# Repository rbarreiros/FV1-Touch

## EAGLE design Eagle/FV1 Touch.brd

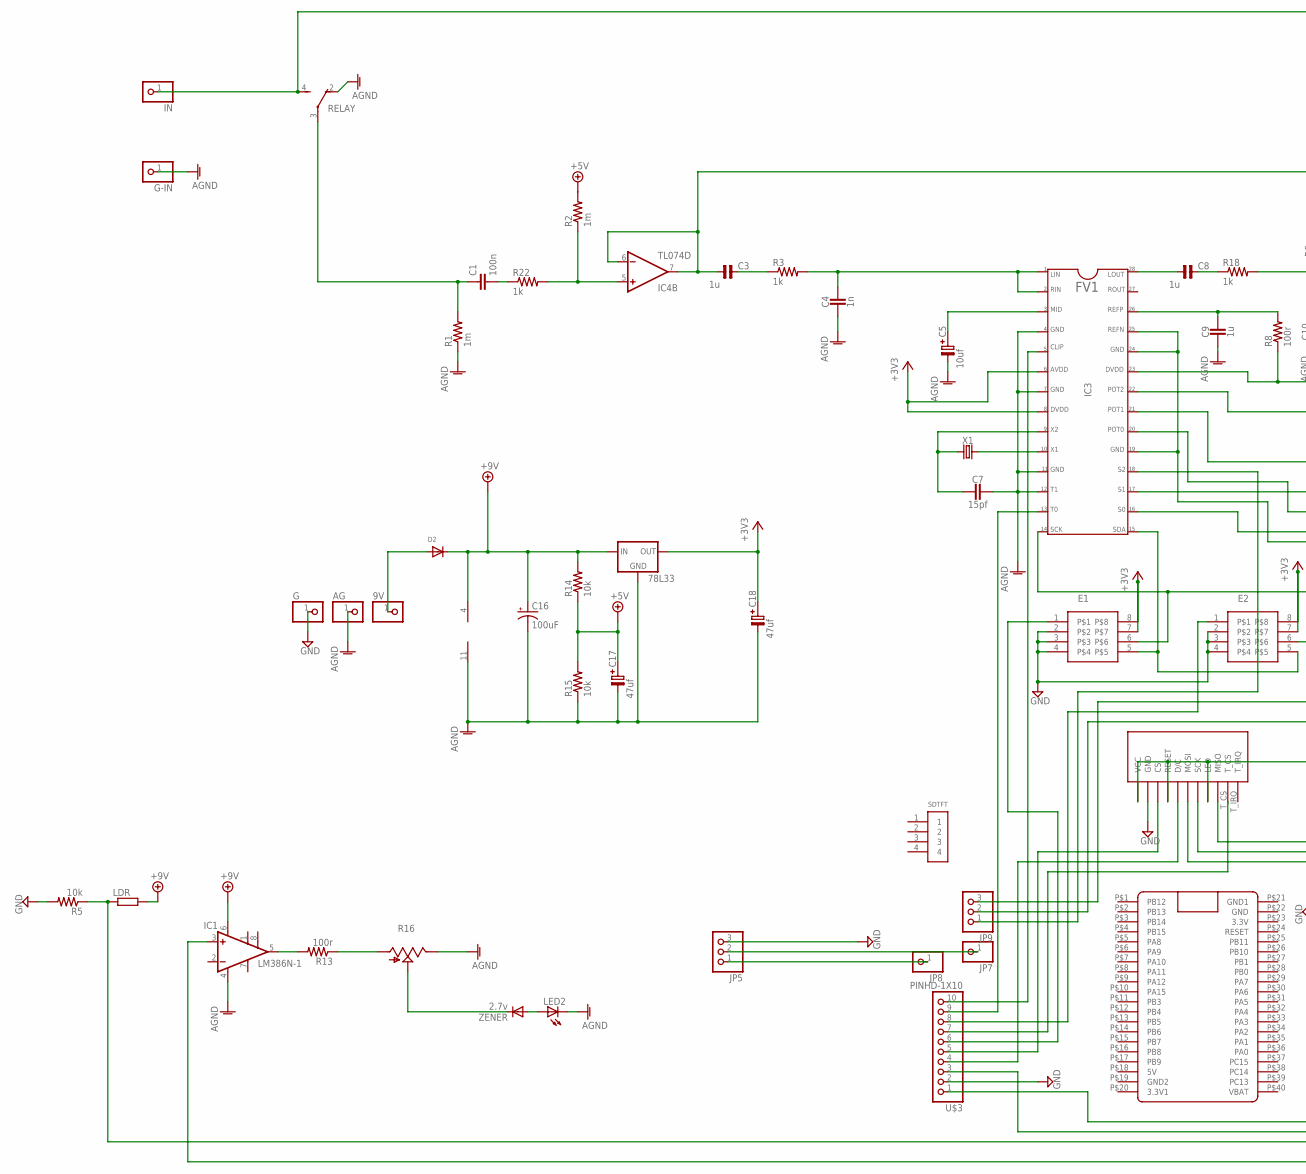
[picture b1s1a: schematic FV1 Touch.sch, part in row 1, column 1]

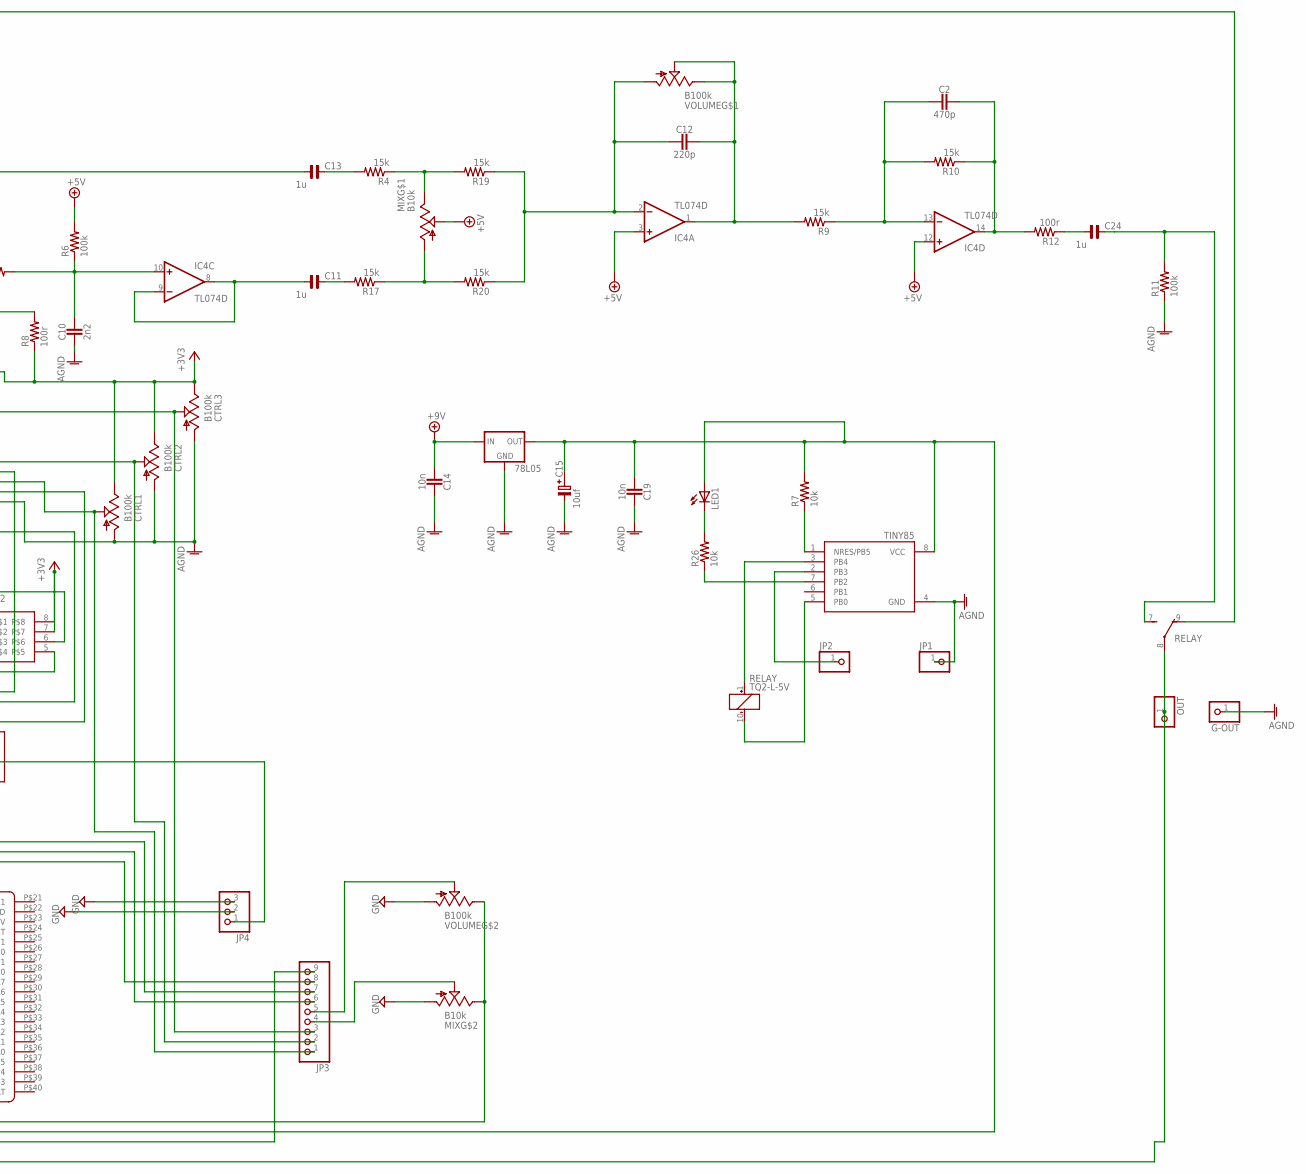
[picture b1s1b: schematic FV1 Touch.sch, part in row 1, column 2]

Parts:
9V: PINHD-1X1; 1X01
78L05, 78L33: 78LXX-SOT89; SOT89
AG: PINHD-1X1; 1X01
C1: 100n; C5B3
C2: 470p; RESISTOR_C1206
C3, C8, C11, C13, C24: 1u; C5,0-7,5X3,0
C4: 1n; RESISTOR_C1206
C5, C15: 10uf; SV-C
C7: 15pf; RESISTOR_C1206
C9: 1u; RESISTOR_C1206
C10: 2n2; RESISTOR_C1206
C12: 220p; RESISTOR_C1206
C14, C19: 10n; RESISTOR_C1206
C16: 100uF; PANASONIC_D
C17, C18: 47uf; SV-C
CTRL1, CTRL2, CTRL3: B100k; 9MM_SNAP-IN_POT
D2: DIODESOD-123; SOD-123
E1, E2: -EEPROM; SOCKED-08
G: PINHD-1X1; 1X01
G-IN: PINHD-1X1; 1X01
G-OUT: PINHD-1X1; 1X01
IC1: LM386N-1; DIL08
IC3: FV1; SO1C28
IC4: TL074D; SO14
IN: PINHD-1X1; 1X01
J1: SPI_TFT_DISPLAY_TOUCH; SPI_DISPLAY_TOUCH
JP1, JP2: PINHD-1X1CB; 1X01-CLEANBIG
JP3: PINHD-1X9; 1X09-BIG
JP4, JP5, JP9: PINHD-1X3; 1X03
JP7, JP8: PINHD-1X1; 1X01
LDR: R-EU_0204/5; 0204/5
LED1, LED2: LED5MM
MIX: B10k; DUAL_9MM_SNAP-IN_POT
OUT: PINHD-1X1; 1X01
R1, R2: 1m; R0805
R3, R18, R22: 1k; R0805
R4, R9, R10, R17, R19, R20: 15k; R0805
R5, R7, R14, R15, R26: 10k; R0805
R6, R11: 100k; R0805
R8, R12, R13: 100r; R0805
R16: TRIM_US-B25P; B25P
RELAY: TQ2-L-5V; TQ2
SDTFT: 1X4-BIG; 1X04-BIG
TINY85: ATTINY85-20P; PDIP08_300MIL
U$1: BLUE_PILL
U$3: PINHD-1X10; 1X10-BIG
VOLUME: B100k; DUAL_9MM_SNAP-IN_POT
X1: CRYSTALPTH-2X6-KIT; CRYSTAL-PTH-2X6-CYL-KIT
ZENER: 2.7v; DO35-7

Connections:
+3V3: 78L33.1 (OUT), C18.+, CTRL1.3 (E), CTRL2.3 (E), CTRL3.3 (E), E1.7, E1.8, E2.7, E2.8, IC3.6, IC3.8, IC3.23, R8.1
+5V: C17.+, IC4.3 (+IN), IC4.12 (+IN), MIX.2 (S), R2.2, R6.2, R14.1, R15.2
+9V: 78L05.3 (IN), 78L33.3 (IN), C14.2, C16.+, D2.C, IC1.6 (VS), IC4.4 (V+), LDR.2, R14.2
AGND: 78L05.2 (GND), 78L33.2 (GND), AG.1, C4.2, C5.-, C7.1, C9.2, C10.2, C14.1, C15.-, C16.-, C17.-, C18.-, C19.1, CTRL1.1 (A), CTRL2.1 (A), CTRL3.1 (A), G-IN.1, G-OUT.1, IC1.4 (GND), IC3.4, IC3.7, IC3.11, IC3.12, IC3.19, IC3.24, IC3.25, IC4.11 (V-), JP1.1, LED2.K (C), R1.1, R11.1, R15.1, R16.E, RELAY.2 (O), TINY85.4 (GND)
GND: E1.2, E1.3, E1.4, E2.2, E2.3, E2.4, G.1, J1.GND, JP4.2, JP4.3, JP5.3, MIX.1B (A), R5.2, U$3.2, VOLUME.1B (A)
GND1: U$1.P$21 (GND1)
unnamed: C1.2, R22.1
unnamed: IC4.5 (+IN), R2.1, R22.2
unnamed: C3.1, C13.1, IC4.6 (-IN), IC4.7 (OUT)
unnamed: C8.1, IC3.28
unnamed: C4.1, IC3.1, IC3.2, R3.2
unnamed: C8.2, R18.1
unnamed: C3.2, R3.1
unnamed: C10.1, IC4.10 (+IN), R6.1, R18.2
unnamed: C11.1, IC4.8 (OUT), IC4.9 (-IN)
unnamed: C11.2, R17.2
unnamed: MIX.1 (A), R17.1, R20.2
unnamed: C24.2, R11.2, RELAY.7 (S)
unnamed: MIX.3 (E), R4.1, R19.2
unnamed: C13.2, R4.2
unnamed: C2.1, IC4.14 (OUT), R10.1, R12.2
unnamed: C24.1, R12.1
unnamed: C1.1, R1.2, RELAY.3
unnamed: C12.2, IC4.2 (-IN), R19.1, R20.1, VOLUME.1 (A)
unnamed: C2.2, IC4.13 (-IN), R9.1, R10.2
unnamed: C12.1, IC4.1 (OUT), R9.2, VOLUME.2 (S), VOLUME.3 (E)
unnamed: J1.CS, U$3.5
unnamed: J1.D/C, U$3.4
unnamed: J1.MOSI, J1.T_MOSI (MOSI), JP3.8
unnamed: C5.+, IC3.3
unnamed: IC3.13, U$3.9
unnamed: CTRL3.2 (S), IC3.22, JP3.3
unnamed: C7.2, IC3.9, X1.1
unnamed: C9.1, IC3.26, R8.2
unnamed: CTRL2.2 (S), IC3.21, JP3.2
unnamed: CTRL1.2 (S), IC3.20, JP3.1
unnamed: J1.SCK, J1.T_SCK (SCK), JP3.6
unnamed: J1.MISO, J1.T_MISO (MISO), JP3.7
unnamed: IC3.10, X1.2
unnamed: J1.T_CS, U$3.7
unnamed: JP5.2, JP7.1
unnamed: E1.6, E2.6, IC3.14
unnamed: E1.5, E2.5, IC3.15
unnamed: JP5.1, JP8.1
unnamed: J1.LED, J1.RESET, J1.VCC, JP4.1
unnamed: IC3.17, JP9.2
unnamed: 9V.1, D2.A
unnamed: IC3.18, JP9.1
unnamed: E1.1, U$3.6
unnamed: JP3.4, MIX.2B (S)
unnamed: 78L05.1 (OUT), C15.+, C19.2, LED1.A, R7.2, TINY85.8 (VCC), U$3.3
unnamed: RELAY.1 (+), TINY85.3 (PB4)
unnamed: R7.1, TINY85.1 (NRES/PB5)
unnamed: RELAY.10 (-), TINY85.5 (PB0)
unnamed: JP2.1, TINY85.2 (PB3)
unnamed: R26.1, TINY85.7 (PB2)
unnamed: LED1.K (C), R26.2
unnamed: IN.1, RELAY.4 (S), RELAY.9 (O)
unnamed: IC1.3 (+IN), OUT.1, RELAY.8
unnamed: JP3.5, VOLUME.2B (S)
unnamed: IC3.16, JP9.3
unnamed: MIX.3B (E), U$3.1, VOLUME.3B (E)
unnamed: R16.S, ZENER.C
unnamed: E2.1, U$3.8
unnamed: IC3.5, U$3.10
unnamed: IC1.5 (OUT), R13.2
unnamed: R13.1, R16.A
unnamed: LED2.A, ZENER.A
unnamed: JP3.9, LDR.1, R5.1

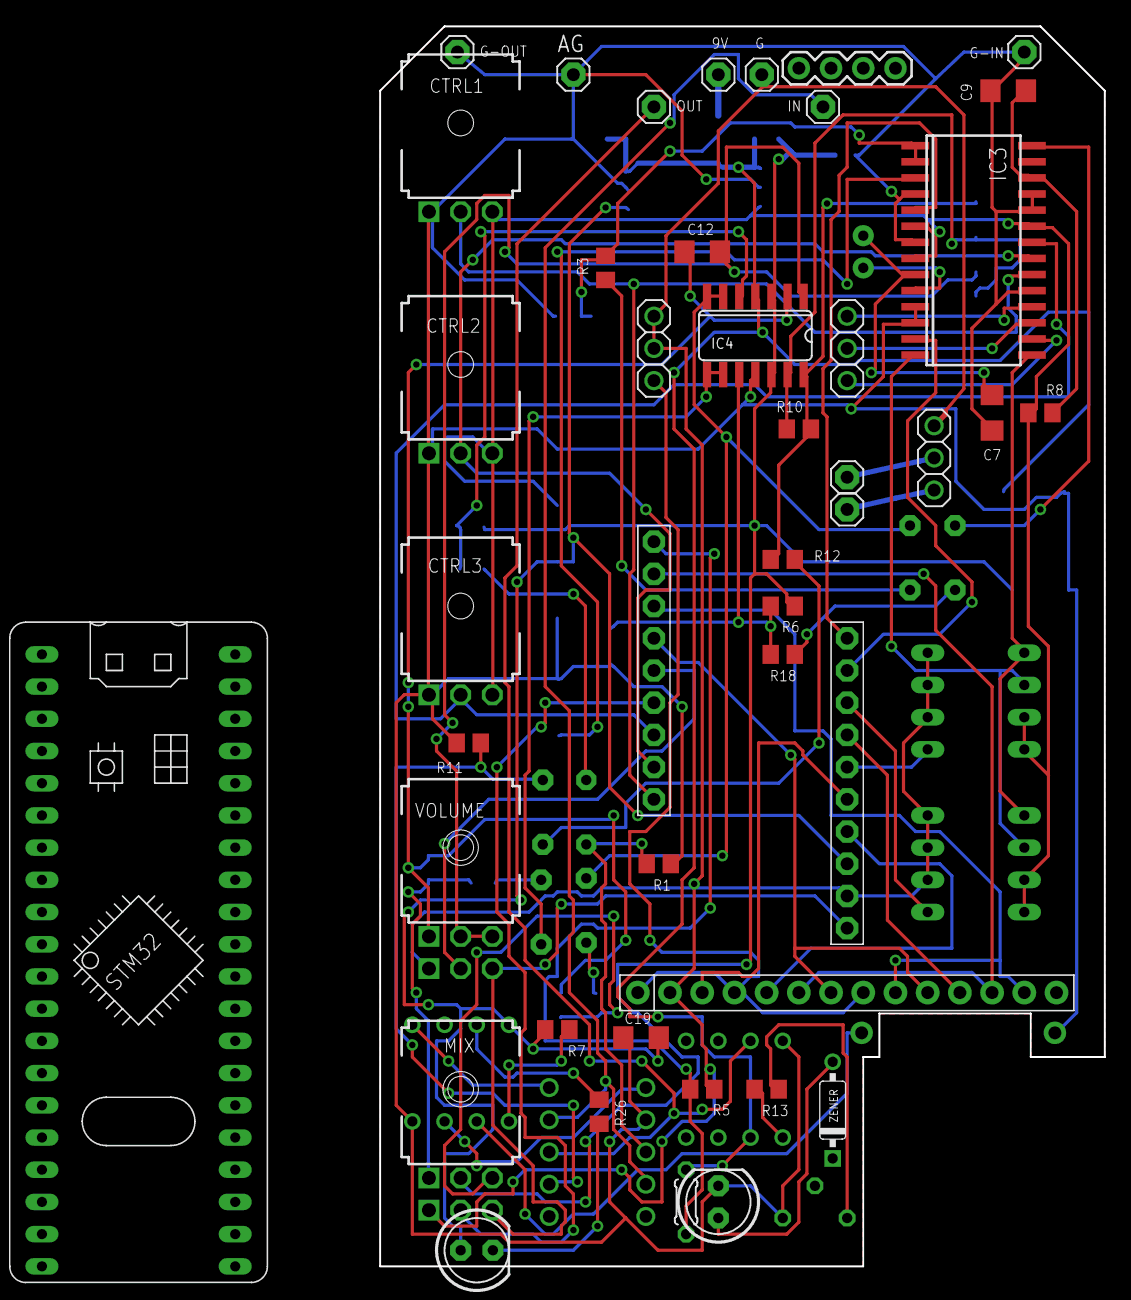
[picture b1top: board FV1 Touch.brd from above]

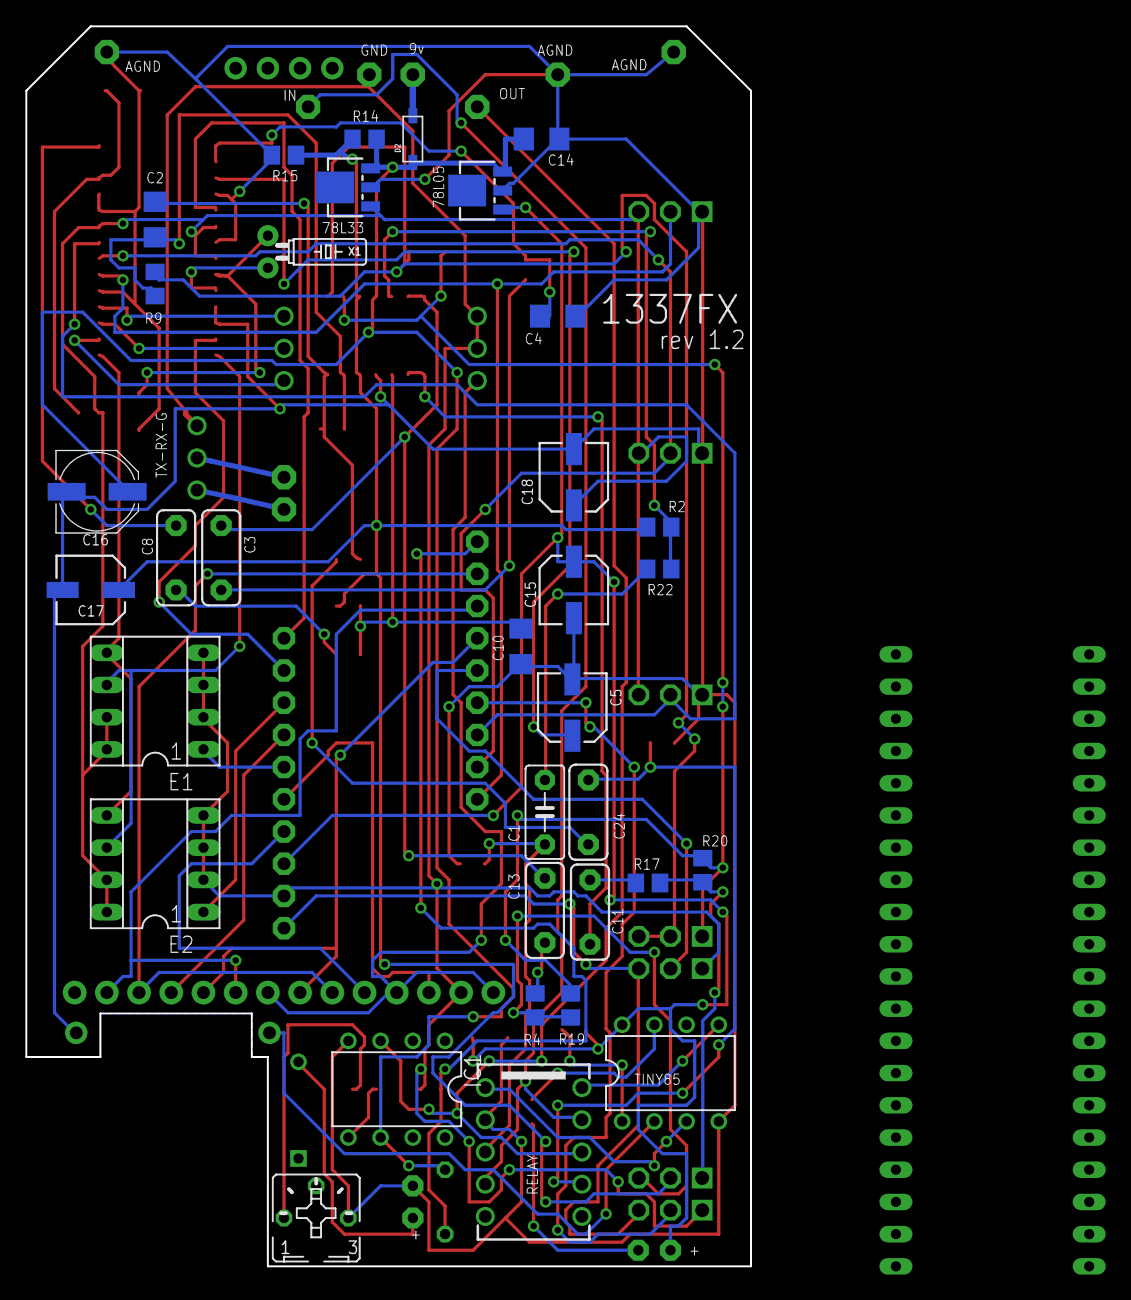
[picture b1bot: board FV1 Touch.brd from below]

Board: 2 copper layers, 57.1 x 97.8 mm, 80 parts (34 on the bottom side), 68 nets.

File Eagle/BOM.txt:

FV1 Touch

Qty Value                 Device                    Package                 Parts                                     Description                                                                                             
                                                                                        
2                         78LXX-SOT89               SOT89                   78L05, 78L33                              VOLTAGE REGULATOR                                                                                       
1                         ATTINY85                  PDIP08_300MIL           TINY85                                    ATMEL ATtiny 85                                                                                         
1                         CRYSTALPTH-2X6-KIT        CRYSTAL-PTH-2X6-CYL-KIT X1                                        Crystals (Generic)  32768Hz                                                                                    
1                         DIODESOD-123              SOD-123                 D2                                        Diode MBR0520LT1G Schottky SMD                                                                                                 
1                         FV1                       SO1C28                  IC3                                                                                                                                               
1                         LED5MM                    LED5MM                  LED                                       LED                                                                                                                                                                                
1                         R-EU_0204/5               0204/5                  LDR                                       LDR RESISTOR                                                                              
1                         TRIM_US-B25P              B25P                    R16                                       POTENTIOMETER TRIMMER 5K                                                                                         
2   -EEPROM               -EEPROM                   SOCKED-DIL08            E1, E2                                                                                                                                            
1   2.7v                  SMALL_DIODEDO35-7         DO35-7                  ZENER                                     Small Signal Diode REVERSE BIASED!!                                                                                                                                                            
3   B100k                 9MM_SNAP-IN_POT_          9MM_SNAP-IN_POT         CTRL1, CTRL2, CTRL3                       9mm vertical snap-in pot, Alpha                                                     
1   B100k                 ALPHA-9MM-DUALPOT         DUAL_9MM_SNAP-IN_POT    VOLUME                                    9mm vertical snap-in pot, Dual Gang
1   B10k                  ALPHA-9MM-DUALPOT         DUAL_9MM_SNAP-IN_POT    MIX                                       9mm vertical snap-in pot, Dual Gang                                                              
1   LM386N-1              LM386N-1                  DIL08                   IC1                                       Low Voltage Audio Power Amplifier                                                                                                                                                  
1   SPI_TFT_DISPLAY_TOUCH SPI_TFT_DISPLAY_TOUCH     SPI_DISPLAY_TOUCH       J1                                        SPI TFT Display with touch 2.4"                                                                             
1   TL074D                TL074D                    SO14                    IC4                                       OP AMP                                                                                                  
1   TQ2-L-5V              TQ2-L-5V                  TQ2                     RELAY                                     LOW PROFILE 2 FORM C RELAY NAiS    
1   STM32F103             BLUEPILL BOARD                                                        

2   100k                  R-US_R0805                R0805                   R6, R11                                   RESISTOR  SMD                                                                           
5   10k                   R-US_R0805                R0805                   R5, R7, R14, R15, R26                     RESISTOR  SMD                                                                                           
3   100r                  R-US_R0805                R0805                   R8, R12, R13                              RESISTOR  SMD                                                                                                                                               
6   15k                   R-US_R0805                R0805                   R4, R9, R10, R17, R19, R20                RESISTOR  SMD                                                                                                                                                                                   
3   1k                    R-US_R0805                R0805                   R3, R18, R22                              RESISTOR  SMD                                                                           
2   1m                    R-US_R0805                R0805                   R1, R2                                    RESISTOR  SMD 

1   100n                  C5/3                      C5B3                    C1                                        CAPACITOR BOX 
2   10n                   CAP1206                   C1206                   C14, C19                                  CAPACITOR SMD 
1   15pf                  CAP1206                   C1206                   C7                                        CAPACITOR SMD 
1   1n                    CAP1206                   C1206                   C4                                        CAPACITOR SMD 
1   1u                    CAP1206                   C1206                   C9                                        CAPACITOR SMD 
1   220p                  CAP1206                   C1206                   C12                                       CAPACITOR SMD                                                                                                        
1   2n2                   CAP1206                   C1206                   C10                                       CAPACITOR SMD                                                                                                        
1   470p                  CAP1206                   C1206                   C2                                        CAPACITOR SMD  

2   47uf                  C-PR-SMD-SV-C             SV-C                    C17, C18                                  47uf polarized capacitors SMD
1   100uF                 100UF-POLAR-25V-20%(ELEC) PANASONIC_D             C16                                       100µF polarized capacitors  SMD                                                                            
2   10uf                  C-PR-SMD-SV-C             SV-C                    C5, C15                                   10uf polarized capacitors  SMD 

5   1u                    C-NP-5,0-7,5X3,0          C5,0-7,5X3,0            C3, C8, C11, C13, C24                     MLCC

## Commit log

2019-11-26 Initial Import
2019-11-27 Moved stuff Cleaned up plenty of code, pretty sure that can be better. Added the relay code
2019-11-27 Added gitignore
2019-11-29 Removed the EEPROM code for the relay switch. Forced input pull up on the relay switch (on pinmode and debounce attach) Added to the repo the compiled version
2019-11-29 Modified pins for the relay for Lee Nonme connections
2019-11-29 Forced effect off after the pin setup
2019-11-29 Moved stuff around to better organize stuff
2019-11-29 Cleanup

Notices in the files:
parts and their libraries:
cap-pan40: Copyright (C) 2004, Bob Starr
SparkFun-Capacitors: Licensing: Creative Commons ShareAlike 4.0 International - https://creativecommons.org/licenses/by-sa/4.0
